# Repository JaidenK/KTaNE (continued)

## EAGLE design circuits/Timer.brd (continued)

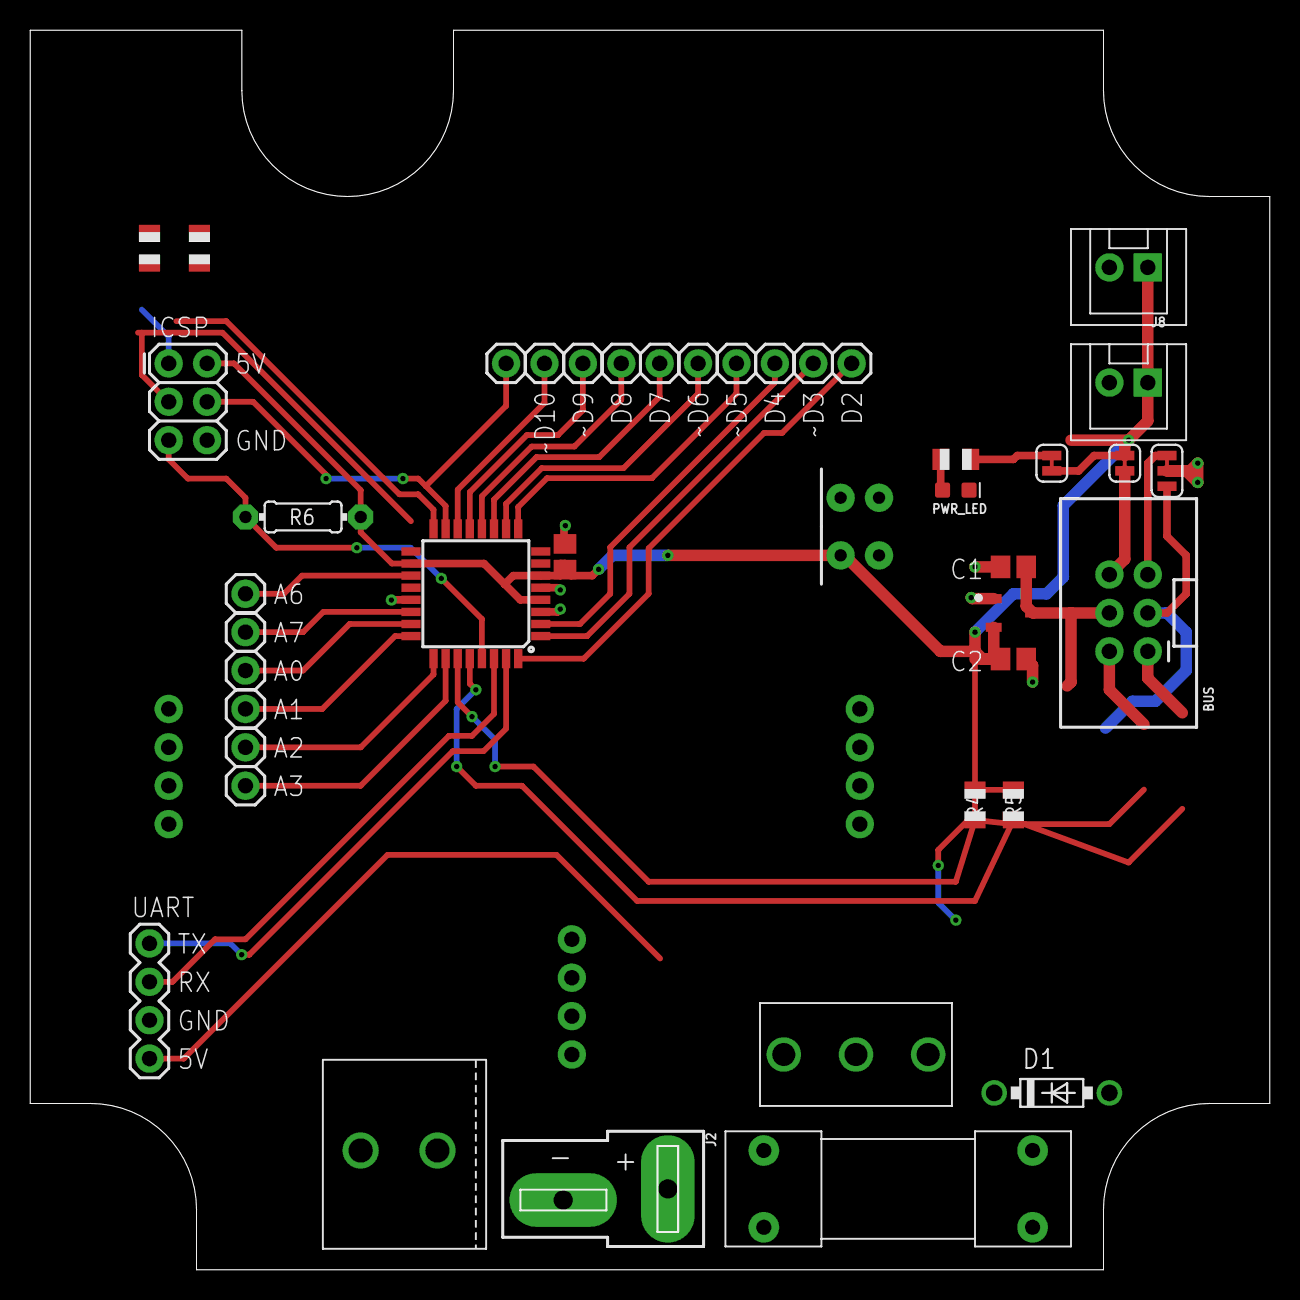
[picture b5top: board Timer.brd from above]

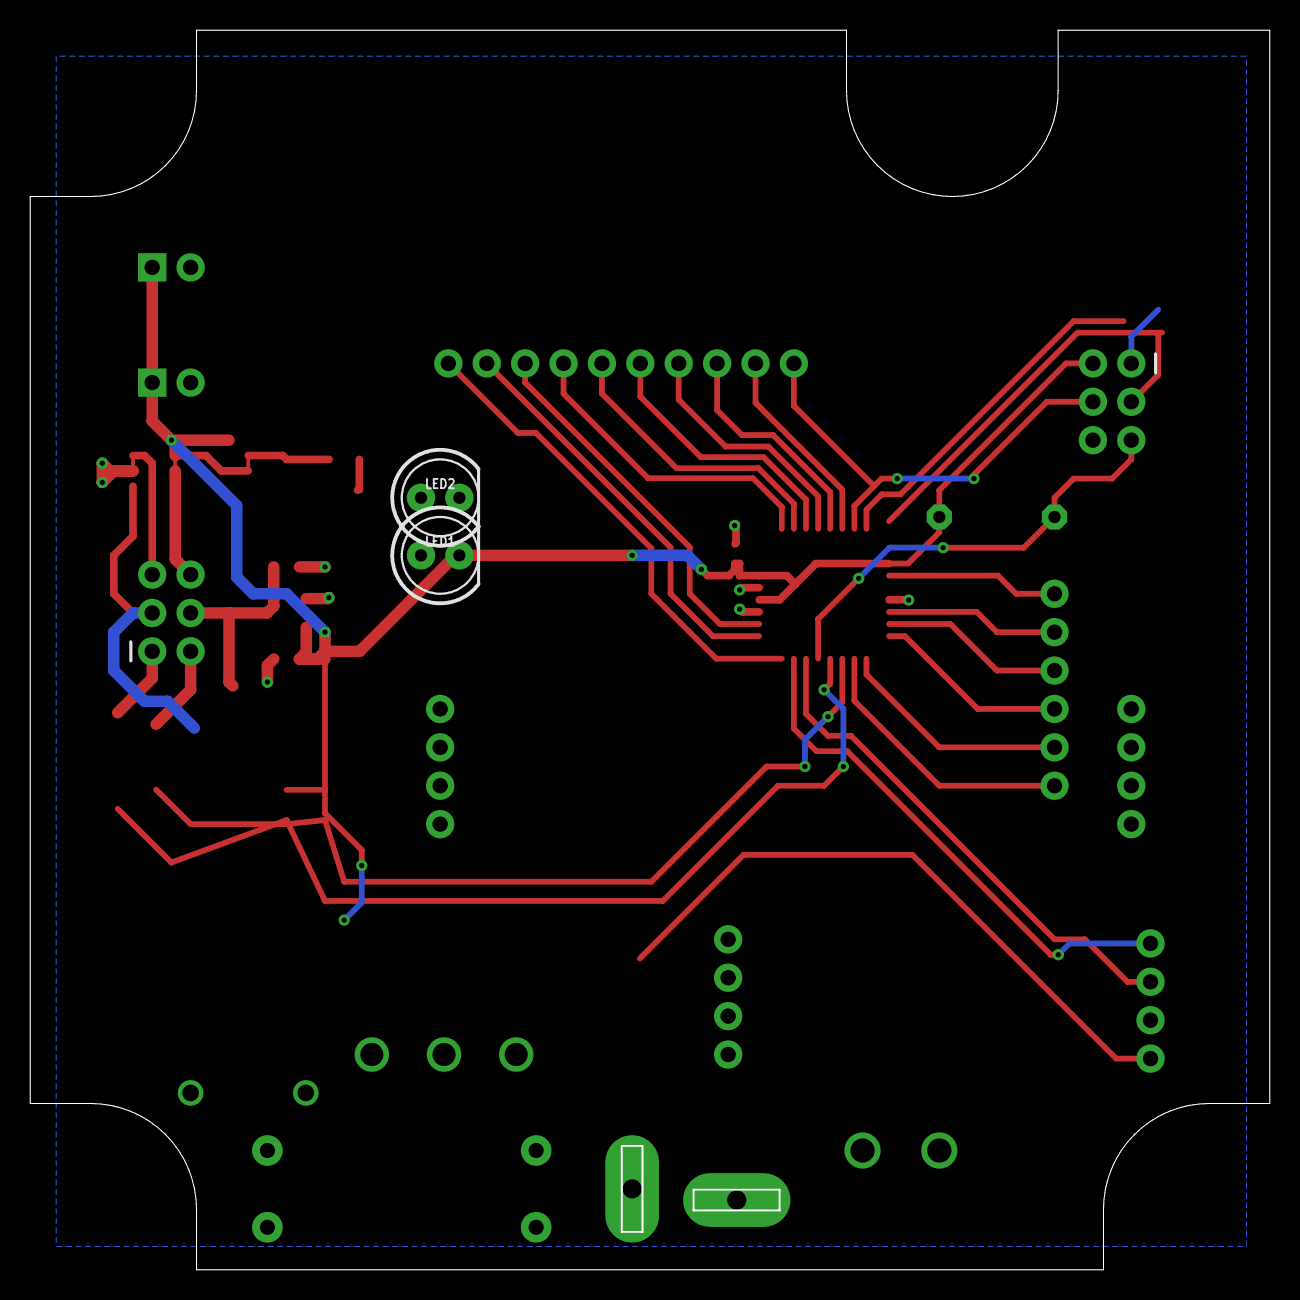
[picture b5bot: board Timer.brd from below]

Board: 2 copper layers, 81.9 x 81.9 mm, 46 parts (2 on the bottom side), 37 nets.

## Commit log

2022-10-16 Initial Commit
    Timer can send commands, receive the responses, and also receive commands asynchronously. Sketchpad sketch exists to conveniently provide events.
2022-10-16 Add missed folder?
2022-10-16 Fix .gitignore
    Wasn't ignoring the correct Arduino libraries
2022-10-16 Add KTaNE folder
    This folder was being missed because it had an old repo in it.
2022-10-16 GUI Console Hello World
    Create a blank window for the GUI console
2022-10-16 Basic serial console clone in WPF
2022-10-16 Add auto-scrolling to text box
2022-10-17 GUI can now receive commands separately from ASCII
2022-10-20 Add Eagle circuit files
2022-10-20 Change Timer I2C address
    I just discovered that General Call is a thing
2022-10-20 Convert serial packet receiving to a state machine
2022-10-20 Sketchpad sends correct strike/disarm commands
2022-10-20 Timer reacts to STRIKE commands
2022-10-20 Add start of relaying UART to I2C
2022-10-22 Add text boxes for RX and TX packets (in addition to the existing ASCII)
2022-10-22 Add test command text box and flash command
2022-10-23 Time limit can be set in EEPROM and is transmitted to GUI at boot up
2022-10-23 Refactor the GUI. Add the IModule interface
2022-10-23 Add serial # and # batteries configurability
2024-12-17 Add build instructions to Readme
2024-12-17 Add documentation link
2024-12-18 Start adding GET_EEPROM command
    Add a button to the GUI to send the GET_EEPROM command, and the start of code to the Timer to receive it. It currently only returns the start of the EEPROM, not the address specified in the argument.
2024-12-18 GET_EEPROM command works for multiple EEPROM Addresses
2024-12-18 Full EEPROM dump from Timer capable
2024-12-18 PC sends the SET_EEPROM command
2024-12-18 Timer receives SET_EEPROM command
2024-12-18 SET_EEPROM command now sets multiple bytes
    Sets timestamp instead of what the user entered in the box
2024-12-19 Timer can forward GET_EEPROM command/response
2024-12-19 Sketchpad can have EEPROM read/written by PC
2024-12-19 Silence some I2C traffic on Timer
2024-12-19 Remove dead code
2024-12-20 Start of parsing EEPROM for GUI display
2024-12-20 GUI can parse user input and set EEPROM value in timer
2024-12-22 Timer can read status register of Sketchpad
2024-12-22 Full game loop can be done with sketchpad
2024-12-23 Button Module initial commit
    Copied from Sketchpad
2024-12-23 Bi-directional I2C starting to work
2024-12-23 Button state machine improvemnets
2024-12-23 GUI adds controls when modules are connected
2024-12-24 GUI can write Button EEPROM
2024-12-24 Timer broadcasts config EEPROM at start of setup
2024-12-24 Button calculates rule and can by configured with GUI
2024-12-24 blink command
2024-12-24 Correct timer pinouts
2024-12-24 Clock is mostly working again
2024-12-25 Timer sends digits on I2C
2024-12-25 Add delay to The Button's LED strip
2024-12-26 The Button seems fully functional
2024-12-27 Library changes and debouncing changes
    KTaNE_InitEEPROM created. It seems to work best when you call it from the initial pseudostate of the FSM.
    Packed the I2C_CommandPacket struct for good measure.
    Button event checker now checks millis to throttle polling rate (makes debounce more predictable)
2024-12-27 Compile images
2024-12-27 Initial commit for keypads
2024-12-27 Keypads responds to all keys on correct channels
2024-12-27 Keypads should be working but there's a bug
    It seems to get the order correct, but it doesn't turn the LED off after a strike and doesn't turn it off when it gets a reset event
2024-12-27 Keypads issue solved
    Don't frickin declare variables inside switch statements
2024-12-27 Allow keypads to have repeated key strokes without generating a strike
2024-12-28 Remove debug print statements
2024-12-28 Remove some unused code
2024-12-28 Trim away some unused code
2024-12-30 Refactor the library a little and add a buzzer beep on startup
2024-12-30 Add self test to the protocol
2024-12-30 Add self test for timer to GUI
2024-12-30 Fix self test
2024-12-30 Tweak self test
2024-12-31 Add Consequence relay to Timer FSM
2024-12-31 Complicated Wires embedded code initial commit
2024-12-31 Fix compilation issues with initial commit
2024-12-31 Implement truth table for Complicated Wires
2024-12-31 Fill in some more Complicated Wires rules logic
2024-12-31 Complicated wires should now write it's letter to memory at game start
2024-12-31 Relocate EEPROM command IDs
2024-12-31 GUI can set Complicated Wire's EEPROM
2024-12-31 I believe Complicated Wires is minspec now
2024-12-31 Solidworks parts
2025-01-01 Create module frame
2025-01-02 Have Timer check for PC connection before starting game
2025-01-02 Solidworks files
2025-01-03 Case parts
2025-01-03 Add side panel part
2025-01-06 Refactor most of the Timer code
2025-01-06 Add some diagrams to the drawio doc
2025-01-07 Tidying up
    Also tweak how Clock flashing works
2025-01-07 Consolidate Arduino Sketches into a single file
    The only difference between them was the name of the board header file.
2025-01-07 Comment and cleanup
2025-01-08 Resolve Button compile errors
    Just making it compile with latest KTaNE library version
2025-01-08 Resolve Keypads compile errors
    No functional change
2025-01-08 Resolve Complicated Wires compile errors
    No functional changes
2025-01-08 Resolve Sketchpad compile error
    No real functional changes, but removed some outdated I2C behavior
2025-01-08 Add some batch files to speed up building the code
2025-01-08 Small refactors
2025-01-09 Refactor GUI code to allow for sequence count tracking
2025-01-10 Add simple ACK system to Serial interface
2025-01-10 Serial thread sends heartbeat
